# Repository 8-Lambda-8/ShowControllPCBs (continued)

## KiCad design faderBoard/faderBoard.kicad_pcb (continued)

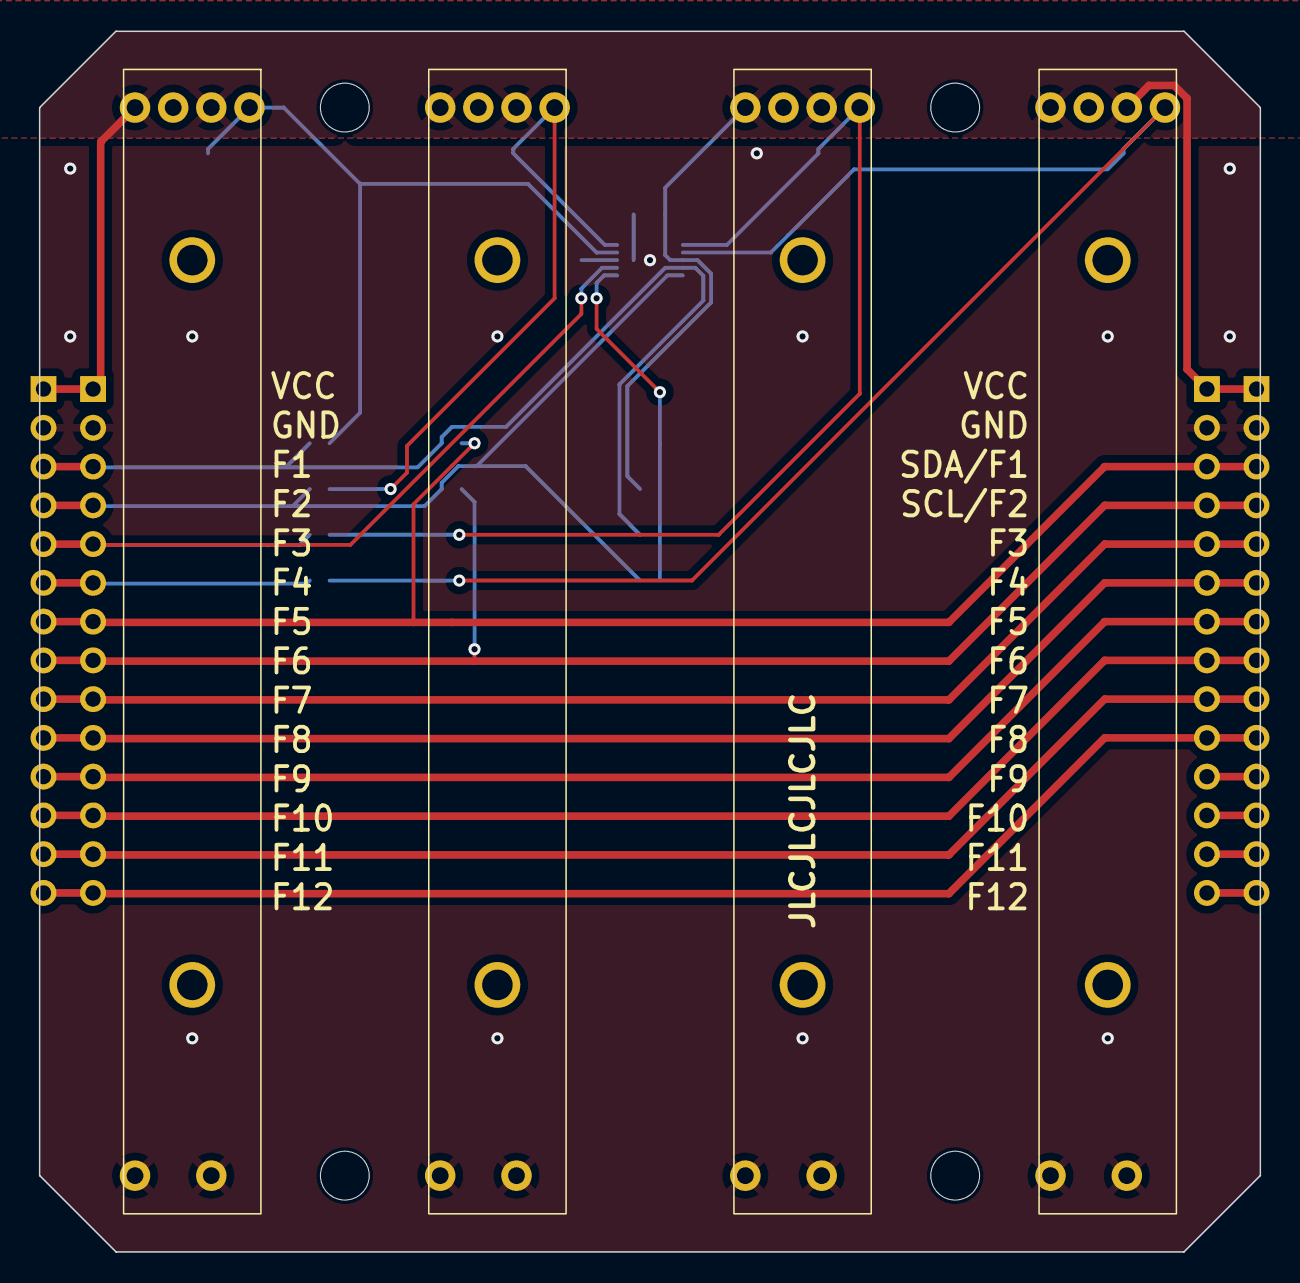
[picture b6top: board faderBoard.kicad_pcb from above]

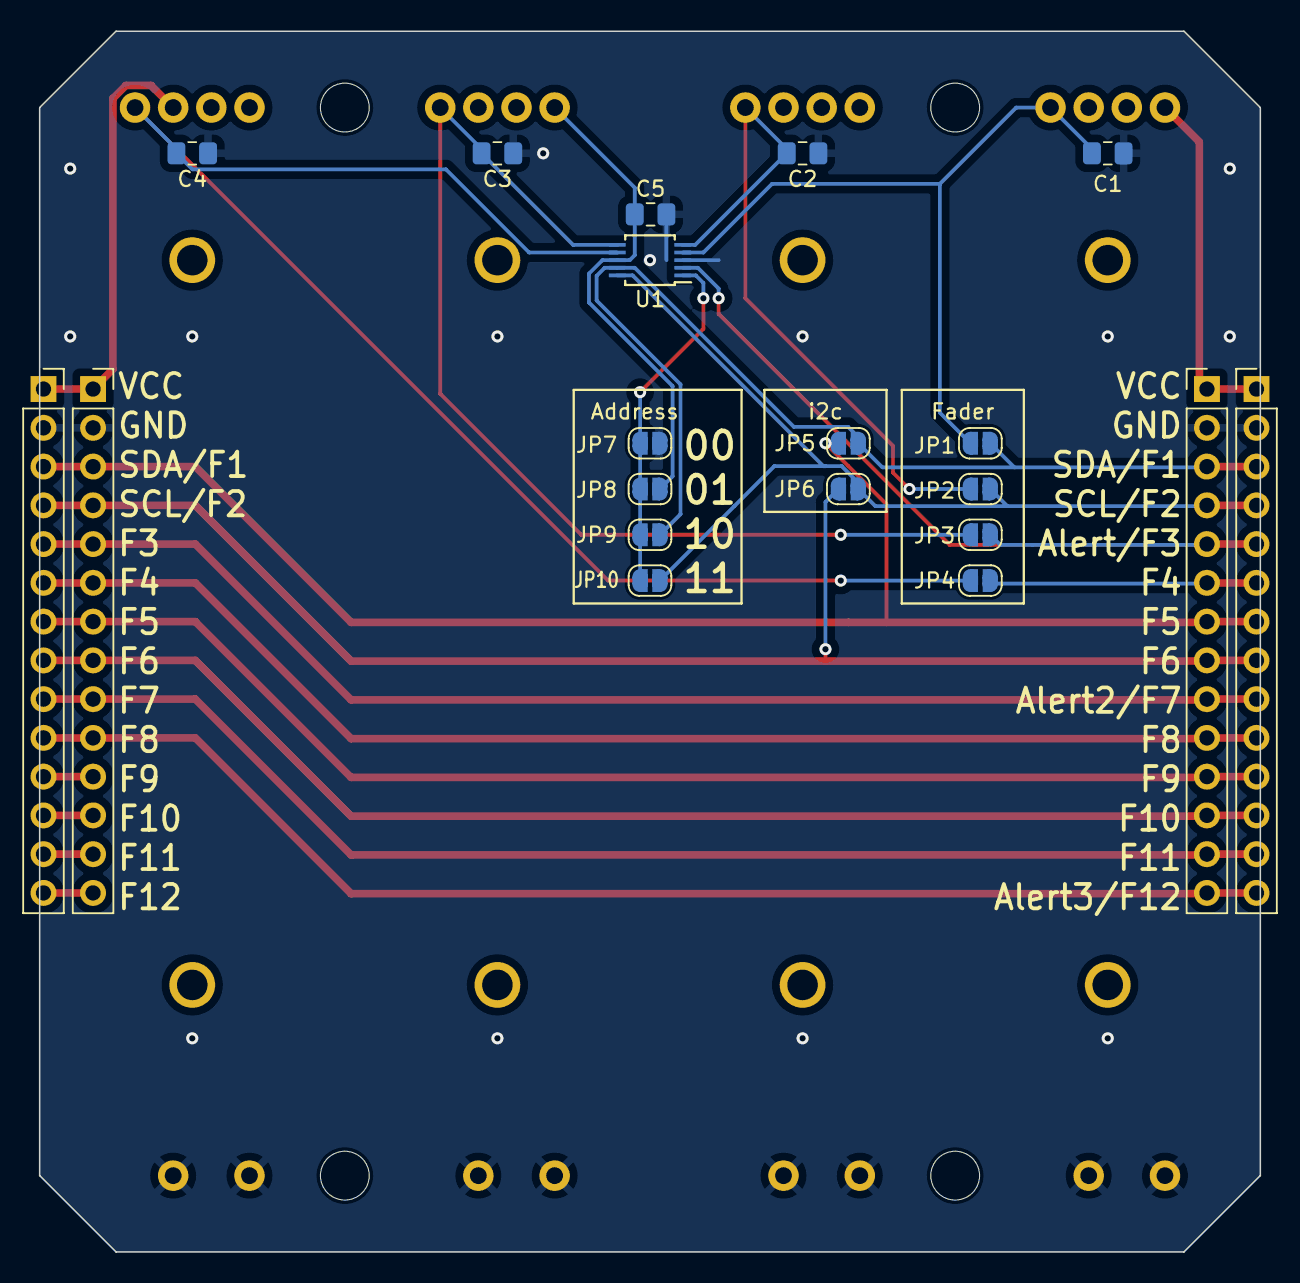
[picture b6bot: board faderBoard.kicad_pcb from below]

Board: 2 copper layers, 80.0 x 80.0 mm, 24 parts (20 on the bottom side), 19 nets.

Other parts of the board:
J1#2: Conn_01x14_Pin; PinHeader_1x14_P2.54mm_Vertical
J2#2: Conn_01x14_Socket; PinSocket_1x14_P2.54mm_Vertical

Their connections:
ALERT: J1#2.5; also elsewhere on the board
GND: J1#2.2, J2#2.2; also elsewhere on the board
unnamed 7: J1#2.9, J2#2.5; also elsewhere on the board
unnamed 8: J1#2.10, J2#2.6; also elsewhere on the board
unnamed 9: J1#2.11, J2#2.7; also elsewhere on the board
unnamed 10: J1#2.12, J2#2.8; also elsewhere on the board
unnamed 11: J1#2.13, J2#2.9; also elsewhere on the board
unnamed 12: J1#2.14, J2#2.10; also elsewhere on the board
SCL: J1#2.4; also elsewhere on the board
SDA: J1#2.3; also elsewhere on the board
VCC: J1#2.1, J2#2.1; also elsewhere on the board
in1: J1#2.7, J2#2.3; also elsewhere on the board
in2: J1#2.8, J2#2.4; also elsewhere on the board
out4: J1#2.6; also elsewhere on the board

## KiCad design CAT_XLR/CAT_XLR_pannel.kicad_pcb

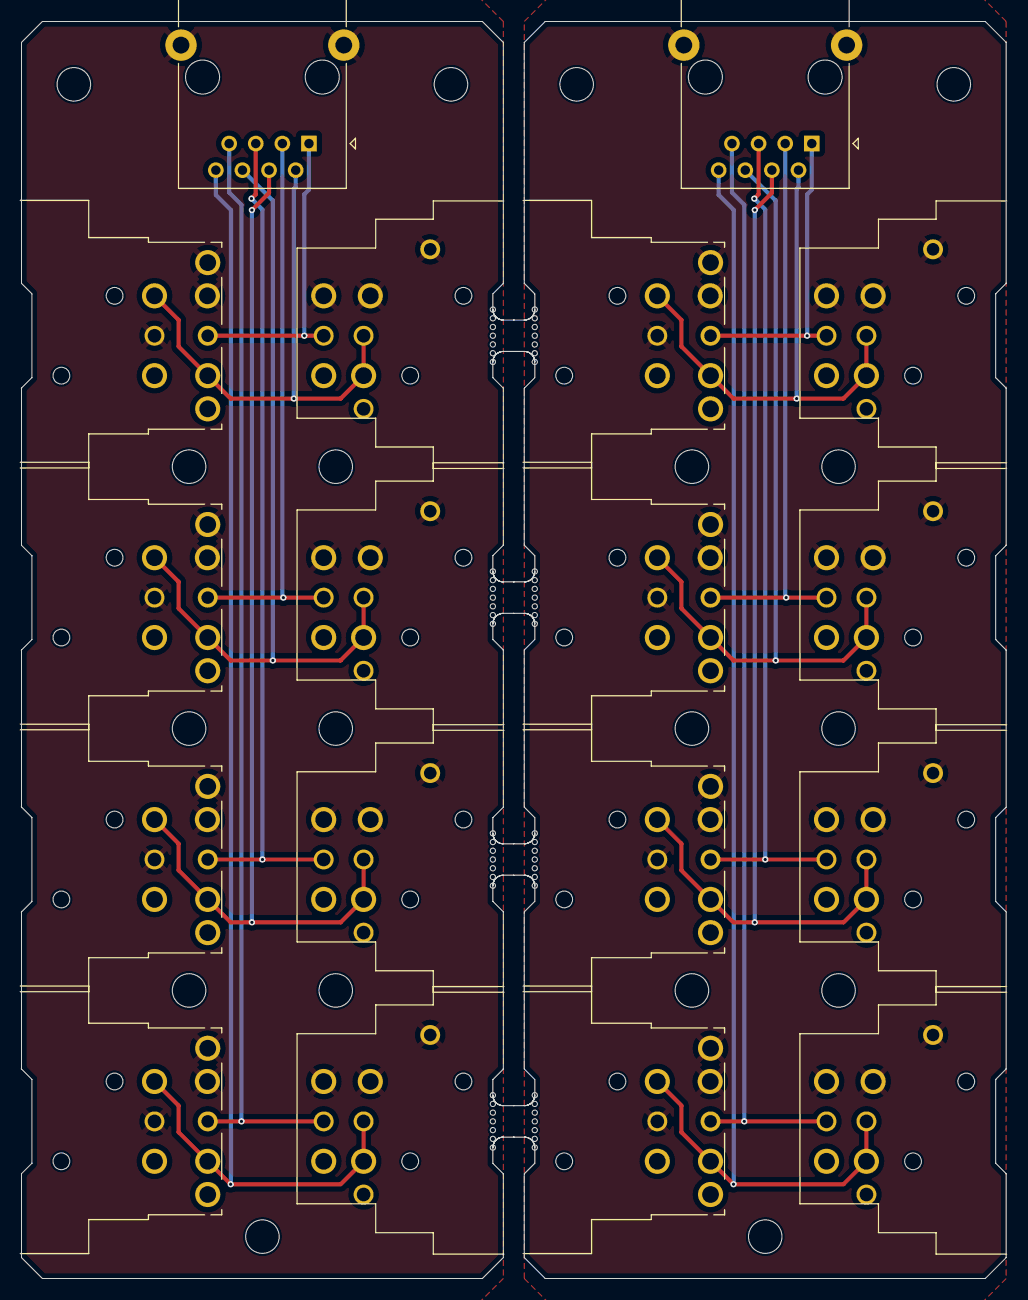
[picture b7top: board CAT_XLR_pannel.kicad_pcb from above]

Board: 2 copper layers, 94.0 x 120.0 mm, 74 parts (0 on the bottom side), 18 nets.

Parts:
J0, J0#2: 8P8C_Shielded; RJ45_Ninigi_GE
J1, J1#2, J2, J2#2, J3, J3#2, J4, J4#2: XLR5; Jack_XLR_Neutrik_NC3+5FAH2-0_Horizontal
J5, J5#2, J6, J6#2, J7, J7#2, J8, J8#2: XLR5; Jack_XLR_Neutrik_NC3+5MAH_Horizontal
KiKit_MB_1_1, KiKit_MB_1_2, KiKit_MB_1_3, KiKit_MB_1_4, KiKit_MB_1_5, KiKit_MB_1_6, KiKit_MB_1_7, KiKit_MB_2_1, KiKit_MB_2_2, KiKit_MB_2_3, KiKit_MB_2_4, KiKit_MB_2_5, KiKit_MB_2_6, KiKit_MB_2_7, KiKit_MB_3_1, KiKit_MB_3_2, KiKit_MB_3_3, KiKit_MB_3_4, KiKit_MB_3_5, KiKit_MB_3_6, KiKit_MB_3_7, KiKit_MB_4_1, KiKit_MB_4_2, KiKit_MB_4_3, KiKit_MB_4_4, KiKit_MB_4_5, KiKit_MB_4_6, KiKit_MB_4_7, KiKit_MB_5_1, KiKit_MB_5_2, KiKit_MB_5_3, KiKit_MB_5_4, KiKit_MB_5_5, KiKit_MB_5_6, KiKit_MB_5_7, KiKit_MB_6_1, KiKit_MB_6_2, KiKit_MB_6_3, KiKit_MB_6_4, KiKit_MB_6_5, KiKit_MB_6_6, KiKit_MB_6_7, KiKit_MB_7_1, KiKit_MB_7_2, KiKit_MB_7_3, KiKit_MB_7_4, KiKit_MB_7_5, KiKit_MB_7_6, KiKit_MB_7_7, KiKit_MB_8_1, KiKit_MB_8_2, KiKit_MB_8_3, KiKit_MB_8_4, KiKit_MB_8_5, KiKit_MB_8_6, KiKit_MB_8_7: NPTH

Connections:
Board_0-DATA+ 1: J0.1, J1#2.3, J5.3
Board_0-DATA+ 2: J0.3, J2.3, J6.3
Board_0-DATA+ 3: J0.5, J3#2.3, J7#2.3
Board_0-DATA+ 4: J0.7, J4.3, J8.3
Board_0-DATA- 1: J0.2, J1#2.2, J5.2
Board_0-DATA- 2: J0.6, J2.2, J6.2
Board_0-DATA- 3: J0.4, J3#2.2, J7#2.2
Board_0-DATA- 4: J0.8, J4.2, J8.2
Board_0-GND: J0.SH, J1#2.1, J1#2.G, J2.1, J2.G, J3#2.1, J3#2.G, J4.1, J4.G, J5.1, J5.G, J6.1, J6.G, J7#2.1, J7#2.G, J8.1, J8.G
Board_1-DATA+ 1: J0#2.1, J1.3, J5#2.3
Board_1-DATA+ 2: J0#2.3, J2#2.3, J6#2.3
Board_1-DATA+ 3: J0#2.5, J3.3, J7.3
Board_1-DATA+ 4: J0#2.7, J4#2.3, J8#2.3
Board_1-DATA- 1: J0#2.2, J1.2, J5#2.2
Board_1-DATA- 2: J0#2.6, J2#2.2, J6#2.2
Board_1-DATA- 3: J0#2.4, J3.2, J7.2
Board_1-DATA- 4: J0#2.8, J4#2.2, J8#2.2
Board_1-GND: J0#2.SH, J1.1, J1.G, J2#2.1, J2#2.G, J3.1, J3.G, J4#2.1, J4#2.G, J5#2.1, J5#2.G, J6#2.1, J6#2.G, J7.1, J7.G, J8#2.1, J8#2.G

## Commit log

2024-01-17 added .gitignore
2024-01-17 created faderBoard
2024-01-17 adder faders
2024-01-17 removed nested folder
2024-01-17 added pinHeaders
2024-01-17 added ADC
2024-01-17 added capacitors
2024-01-17 added in i2c connenciton
2024-01-17 added footprints
2024-01-17 placed faders
2024-01-17 placed pinHeaders
2024-01-17 placed fader caps
2024-01-17 placed adc
2024-01-17 fixed pin connection
2024-01-17 routing
2024-01-18 labels and fixes
2024-01-20 connected Alert pin
2024-01-20 created buttonMatrixBoard
2024-02-06 created touchBoard
2024-02-06 created touch matrix
2024-02-11 added production to gitignore
2024-02-11 fader board small changes
2024-02-11 created touch board
2024-02-11 fader board changes
2024-02-11 created buttonMatrix pannel
2024-02-11 touchboard added leds
2024-02-29 fixed footprint problems on first order
2024-02-29 added created ibom
2024-02-29 added BOM Links to readme
2024-02-29 buttonMatrix changed Diode footprint
2024-02-29 buttonMatrix improved bord improved border pads for joining boards
2024-02-29 updated ibom
2024-02-29 buttonMatrix added mounting holes
2024-03-03 added more edge connections
2024-03-03 updated pannel and ibom
2024-03-04 some updates
2024-03-10 added buttonMatrix library
2024-03-15 added fader library
2024-03-15 fixed buttonMatrix library
2024-03-27 fixed button matrix lib (again)
2024-03-29 inverted button state
2024-03-30 Create LICENSE
2024-10-19 added CAT-XLR Adapter board
2024-10-22 fixed CAT connection and gnd connection
2024-10-22 added link to CAT-XLR iBOM
2025-12-22 created motorFaderBoard
2025-12-29 pcb and stuff
2025-12-30 connectors, labels, vias
2026-06-19 added DJ-Mixer
